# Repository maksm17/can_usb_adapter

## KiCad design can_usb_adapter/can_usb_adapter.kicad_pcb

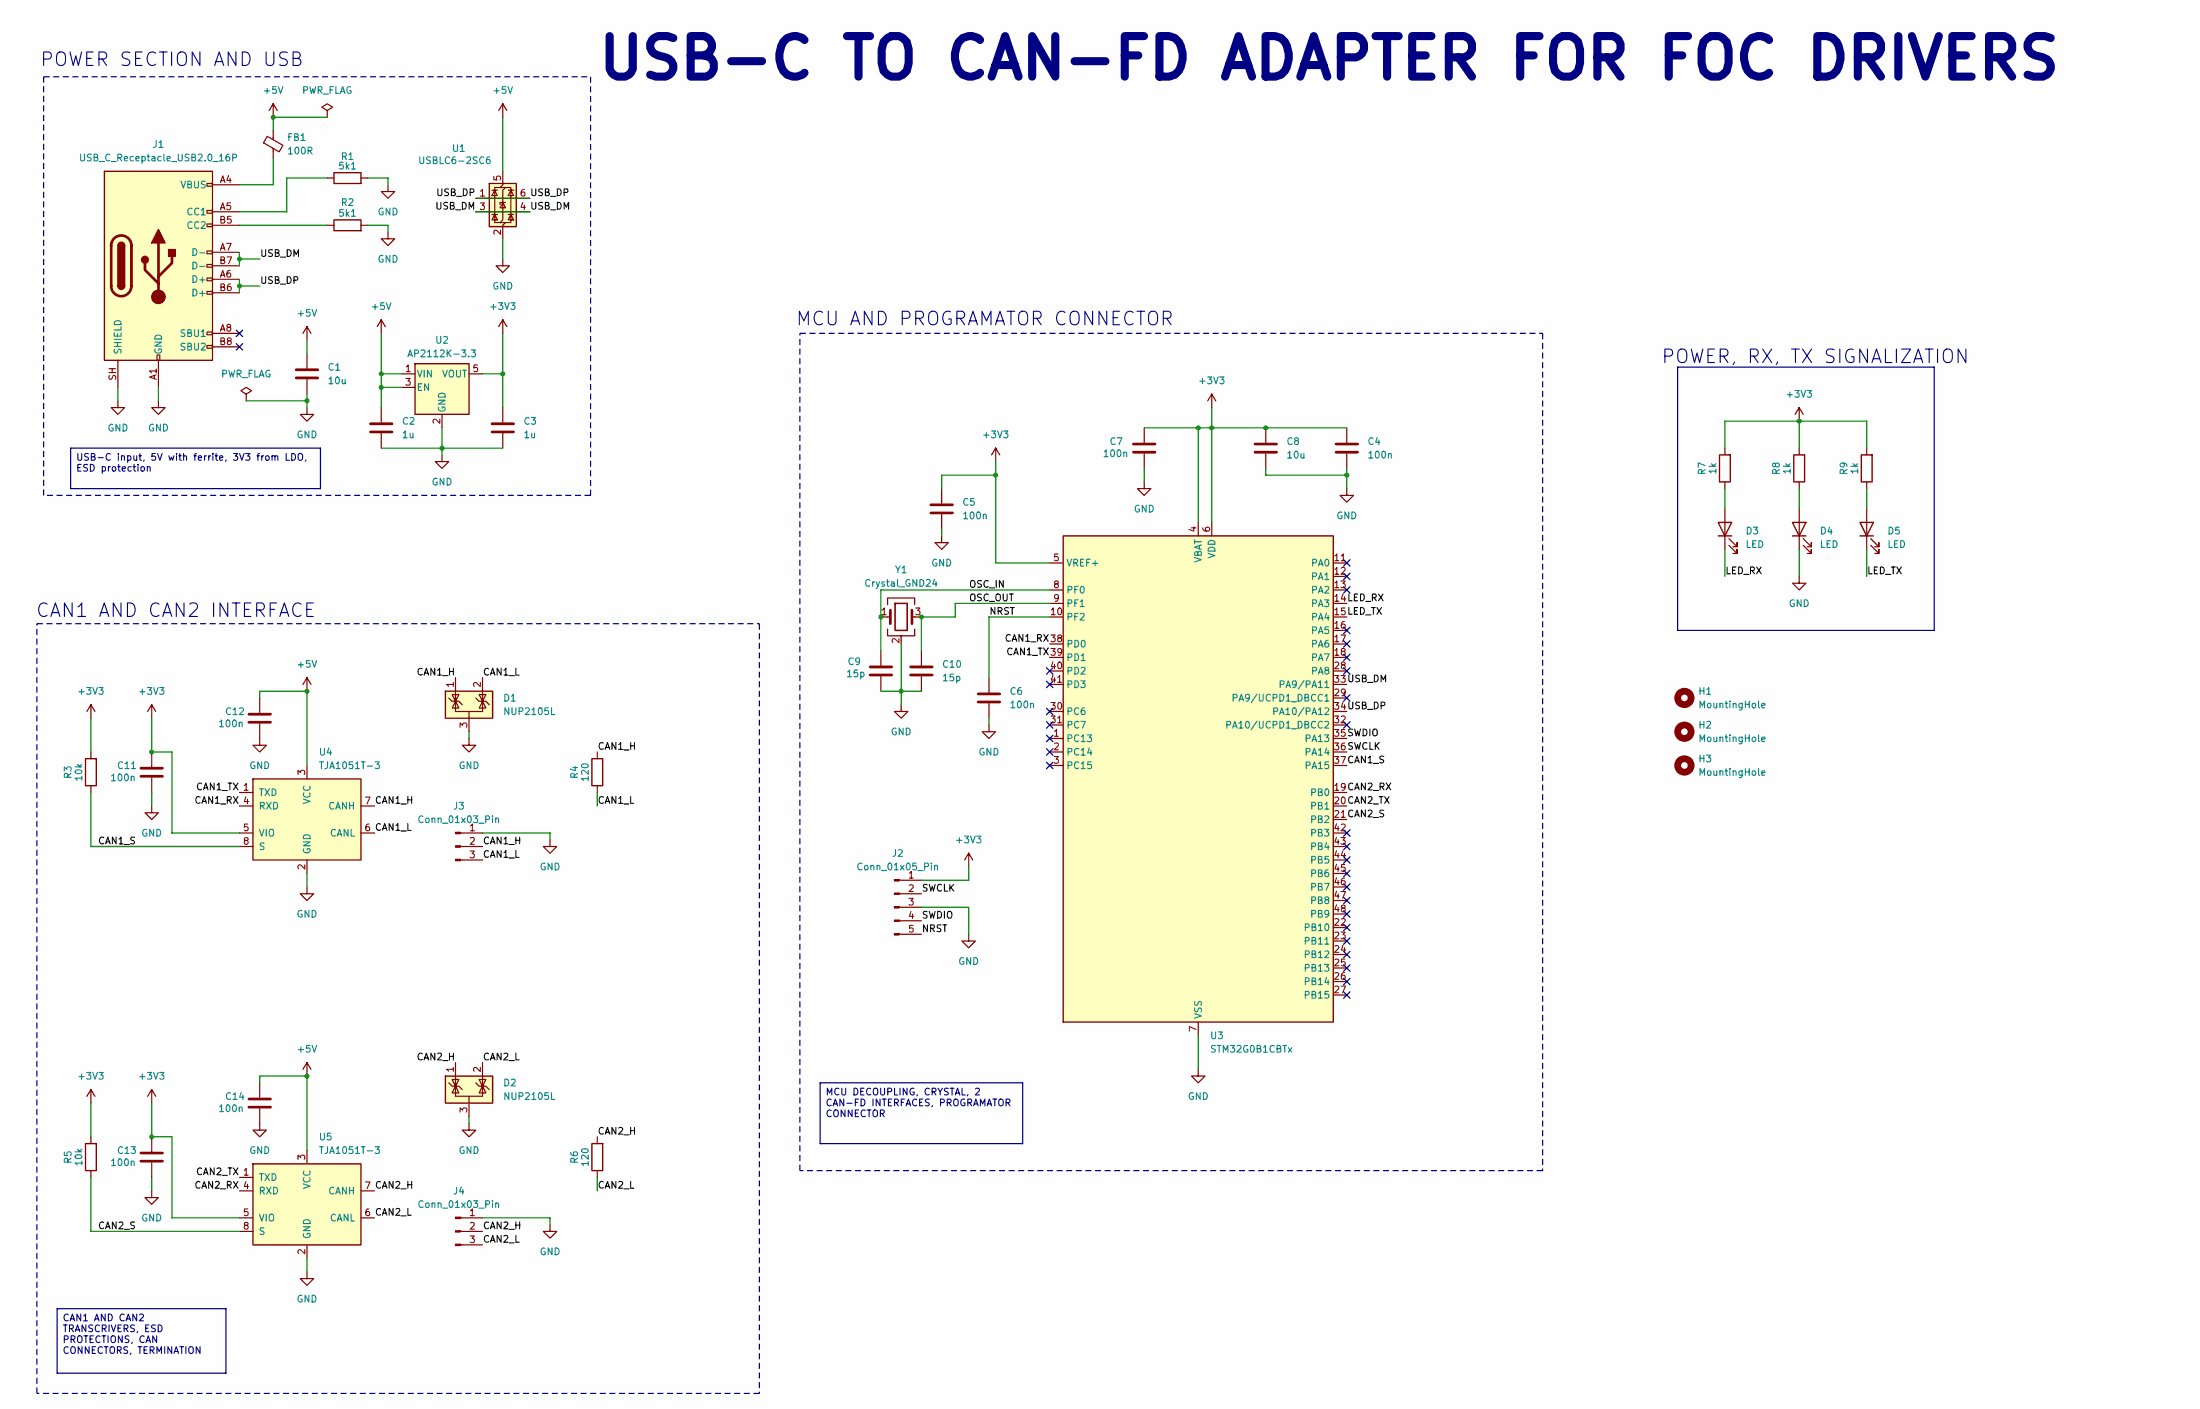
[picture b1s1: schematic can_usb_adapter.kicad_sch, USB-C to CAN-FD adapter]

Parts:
C1, C8: 10u; C_0805_2012Metric
C2, C3: 1u; C_0603_1608Metric
C4, C5, C6, C7, C11, C12, C13, C14: 100n; C_0603_1608Metric
C9, C10: 15p; C_0603_1608Metric
D1, D2: NUP2105L; SOT-23
D3, D4, D5: LED; LED_0603_1608Metric
FB1: 100R; L_0805_2012Metric
H1, H2, H3: MountingHole; MountingHole_2.2mm_M2
J1: USB_C_Receptacle_USB2.0_16P; USB_C_Receptacle_HRO_TYPE-C-31-M-12
J2: Conn_01x05_Pin; PinHeader_1x05_P2.54mm_Vertical
J3, J4: Conn_01x03_Pin; JST_GH_SM03B-GHS-TB_1x03-1MP_P1.25mm_Horizontal
R1, R2: 5k1; R_0603_1608Metric
R3, R5: 10k; R_0603_1608Metric
R4, R6: 120; R_0603_1608Metric
R7, R8, R9: 1k; R_0603_1608Metric
U1: USBLC6-2SC6; SOT-23-6
U2: AP2112K-3.3; SOT-23-5
U3: STM32G0B1CBTx; LQFP-48_7x7mm_P0.5mm
U4, U5: TJA1051T-3; SOIC-8_3.9x4.9mm_P1.27mm
Y1: Crystal_GND24; Crystal_SMD_3225-4Pin_3.2x2.5mm

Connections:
+3V3: C3.1, C4.1, C5.1, C7.2, C8.1, C11.2, C13.2, J2.1, R3.2, R5.2, R7.2, R8.2, R9.2, U2.5 (VOUT), U3.4 (VBAT), U3.5 (VREF+), U3.6 (VDD), U4.5 (VIO), U5.5 (VIO)
+5V: C1.1, C2.1, C12.2, C14.2, FB1.1, U1.5 (VBUS), U2.1 (VIN), U2.3 (EN), U4.3 (VCC), U5.3 (VCC)
/CAN1_H: D1.1 (K), J3.2, R4.2, U4.7 (CANH)
/CAN1_L: D1.2 (K), J3.3, R4.1, U4.6 (CANL)
/CAN1_RX: U3.38 (PD0), U4.4 (RXD)
/CAN1_S: R3.1, U3.37 (PA15), U4.8 (S)
/CAN1_TX: U3.39 (PD1), U4.1 (TXD)
/CAN2_H: D2.1 (K), J4.2, R6.2, U5.7 (CANH)
/CAN2_L: D2.2 (K), J4.3, R6.1, U5.6 (CANL)
/CAN2_RX: U3.19 (PB0), U5.4 (RXD)
/CAN2_S: R5.1, U3.21 (PB2), U5.8 (S)
/CAN2_TX: U3.20 (PB1), U5.1 (TXD)
/LED_RX: D3.1 (K), U3.14 (PA3)
/LED_TX: D5.1 (K), U3.15 (PA4)
/NRST: C6.1, J2.5, U3.10 (PF2)
/OSC_IN: C9.1, U3.8 (PF0), Y1.1
/OSC_OUT: C10.1, U3.9 (PF1), Y1.3
/SWCLK: J2.2, U3.36 (PA14)
/SWDIO: J2.4, U3.35 (PA13)
/USB_DM: J1.A7 (D-), J1.B7 (D-), U1.3 (I/O2), U1.4 (I/O2), U3.33 (PA9/PA11)
/USB_DP: J1.A6 (D+), J1.B6 (D+), U1.1 (I/O1), U1.6 (I/O1), U3.34 (PA10/PA12)
GND: C1.2, C2.2, C3.2, C4.2, C5.2, C6.2, C7.1, C8.2, C9.2, C10.2, C11.1, C12.1, C13.1, C14.1, D1.3 (A), D2.3 (A), D4.1 (K), J1.A1 (GND), J1.A12 (GND), J1.B1 (GND), J1.B12 (GND), J1.SH (SHIELD), J2.3, J3.1, J4.1, R1.2, R2.2, U1.2 (GND), U2.2 (GND), U3.7 (VSS), U4.2 (GND), U5.2 (GND), Y1.2 (G), Y1.4 (G)
unnamed: D3.2 (A), R7.1
unnamed: D4.2 (A), R8.1
unnamed: D5.2 (A), R9.1
unnamed: FB1.2, J1.A4 (VBUS), J1.A9 (VBUS), J1.B4 (VBUS), J1.B9 (VBUS)
unnamed: J1.A5 (CC1), R1.1
unnamed: J1.B5 (CC2), R2.1

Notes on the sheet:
POWER SECTION AND USB
CAN1 AND CAN2 INTERFACE
USB-C TO CAN-FD ADAPTER FOR FOC DRIVERS
POWER, RX, TX SIGNALIZATION
MCU AND PROGRAMATOR CONNECTOR
CAN1 AND CAN2 TRANSCRIVERS, ESD PROTECTIONS, CAN CONNECTORS, TERMINATION
USB-C input, 5V with ferrite, 3V3 from LDO, ESD protection
MCU DECOUPLING, CRYSTAL, 2 CAN-FD INTERFACES, PROGRAMATOR CONNECTOR

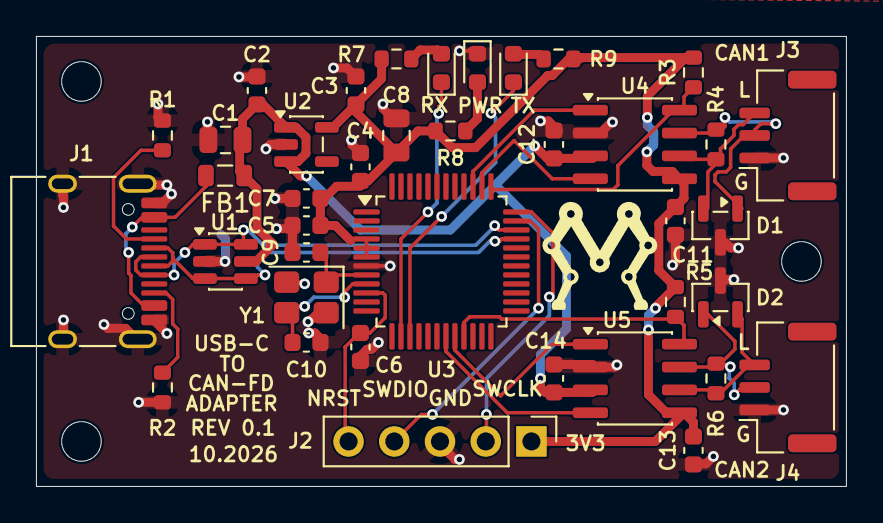
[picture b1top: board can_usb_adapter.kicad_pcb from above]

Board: 2 copper layers, 45.0 x 25.0 mm, 42 parts (0 on the bottom side), 28 nets.

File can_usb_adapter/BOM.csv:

Comment,Designator,Footprint,LCSC Part #
100nF 50V X7R,"C4,C5,C6,C7,C11,C12,C13,C14",C_0603_1608Metric,C14663
1uF 25V X5R,"C2,C3",C_0603_1608Metric,C15849
10uF 10V X5R,"C1,C8",C_0805_2012Metric,C15850
15pF 50V C0G,"C9,C10",C_0603_1608Metric,C1644
PESD2CANFD24V-T (CAN ESD),"D1,D2",SOT-23,C5180309
LED red 0603 (KT-0603R),"D3,D4,D5",LED_0603_1608Metric,C2286
Ferrite 100R@100MHz 0805 800mA (GZ2012D101TF),FB1,L_0805_2012Metric,C1015
USB-C HRO TYPE-C-31-M-12,J1,USB_C_Receptacle_HRO_TYPE-C-31-M-12,C165948
JST GH SM03B-GHS-TB,"J3,J4",JST_GH_SM03B-GHS-TB_1x03-1MP_P1.25mm_Horizontal,C514175
5.1kOhm 1% 0603,"R1,R2",R_0603_1608Metric,C23186
10kOhm 1% 0603,"R3,R5",R_0603_1608Metric,C25804
120Ohm 1% 0603,"R4,R6",R_0603_1608Metric,C22787
1kOhm 1% 0603,"R7,R8,R9",R_0603_1608Metric,C21190
USBLC6-2SC6,U1,SOT-23-6,C7519
AP2112K-3.3TRG1,U2,SOT-23-5,C23380830
STM32G0B1CBT6,U3,LQFP-48_7x7mm_P0.5mm,C2847904
TJA1051T/3,"U4,U5",SOIC-8_3.9x4.9mm_P1.27mm,C5342108
8MHz crystal 3225,Y1,Crystal_SMD_3225-4Pin_3.2x2.5mm,C57131

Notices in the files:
can_usb_adapter/can_usb_adapter.kicad_pcb:
Pin mapping based on candleLightFD by Linux Automation (CERN OHL v1.2)
